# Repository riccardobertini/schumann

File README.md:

# Schumann Resonance Generator 🌍⚡  

This project was created with the idea of building **a simple yet interesting electronic device** capable of locally generating the most well-known **Schumann Resonance** frequencies, using the **Arduino** platform and easily available components.

> ⚠️ **Important note**  
> This project **is not a medical device** and makes no scientific claims. It is intended solely as an **electronic and educational experiment**.

---

## 📡 What Is the Schumann Resonance

The Schumann Resonance is a natural phenomenon discovered in the 1950s by physicist **Winfried Otto Schumann**.  
The Earth and the ionosphere behave like a kind of **natural cavity** in which certain electromagnetic frequencies can stabilize.

The most famous one is:
- **7.83 Hz** → fundamental frequency

Among the most well-known harmonics:
- **14.1 Hz**

These frequencies belong to the **ELF (Extremely Low Frequency)** category.

---

## 🤔 Why Does This Project Interest So Many People?

Online there are countless discussions, videos, and forums that attribute various **possible subjective effects** to the Schumann Resonance, often based on personal experiences.

The most common ones include:
- relaxation,
- improved sleep,
- stress reduction,
- increased concentration,
- a general sense of well-being.

👉 **Important:**  
These effects **are not scientifically proven**. However, curiosity and interest in these topics pushed me to experiment firsthand.

This project was born with exactly this mindset:  
**curiosity, DIY spirit, and conscious experimentation**.

---

## 🛠️ What This Generator Can Be Used For

The generator can be used in different contexts:

- **Educational Arduino project**  
  A great example of:
  - low-frequency signal generation,
  - interrupt handling for time synchronization,
  - control logic.

- **Personal experiment**  
  Some users use it in home environments (study, relaxation area, bedroom) to observe any subjective sensations.

- **Maker / DIY project**  
  Perfect as a base for:
  - adding a display,
  - Bluetooth or Wi-Fi control,
  - battery power,
  - integration into home automation projects.

- **Shielded or isolated environments**  
  Used by people working in spaces with strong electromagnetic shielding.

---

## ⚙️ Features

The device includes the following modes:

- 🔁 **Automatic dual frequency**
  - cyclic alternation between **7.83 Hz** and **14.1 Hz**

- 🎯 **Fixed frequency 7.83 Hz**

- 🎯 **Fixed frequency 14.1 Hz**

- 🌙 **LED shutdown during nighttime**
  - useful if the device is used in dark environments or during sleep hours

---

## 🔌 Hardware

The project uses:
- **Arduino Micro–compatible** microcontroller,
- simple electronic components,
- status LEDs,
- essential controls for mode selection.

The **electronic schematics** are available in the repository.

---

## 💻 Software

The firmware is developed in:
- **C++**
- **Arduino platform**

The code is designed to be:
- readable,
- easy to modify.

It manages:
- frequency generation,
- automatic switching,
- mode selection,
- LED control.

---

The repository includes:
- source code,
- electronic schematics,
- Gerber files for PCB manufacturing,
- STL files for enclosure creation.

Contributions, forks, and improvements are welcome 🚀

---

## 🖼️ Images of the Finished Project

Below are some images of the assembled and working device.

### General view

### Electronic board detail

### Device in operation

> 📌 Images are located in the `/images` folder of the repository.

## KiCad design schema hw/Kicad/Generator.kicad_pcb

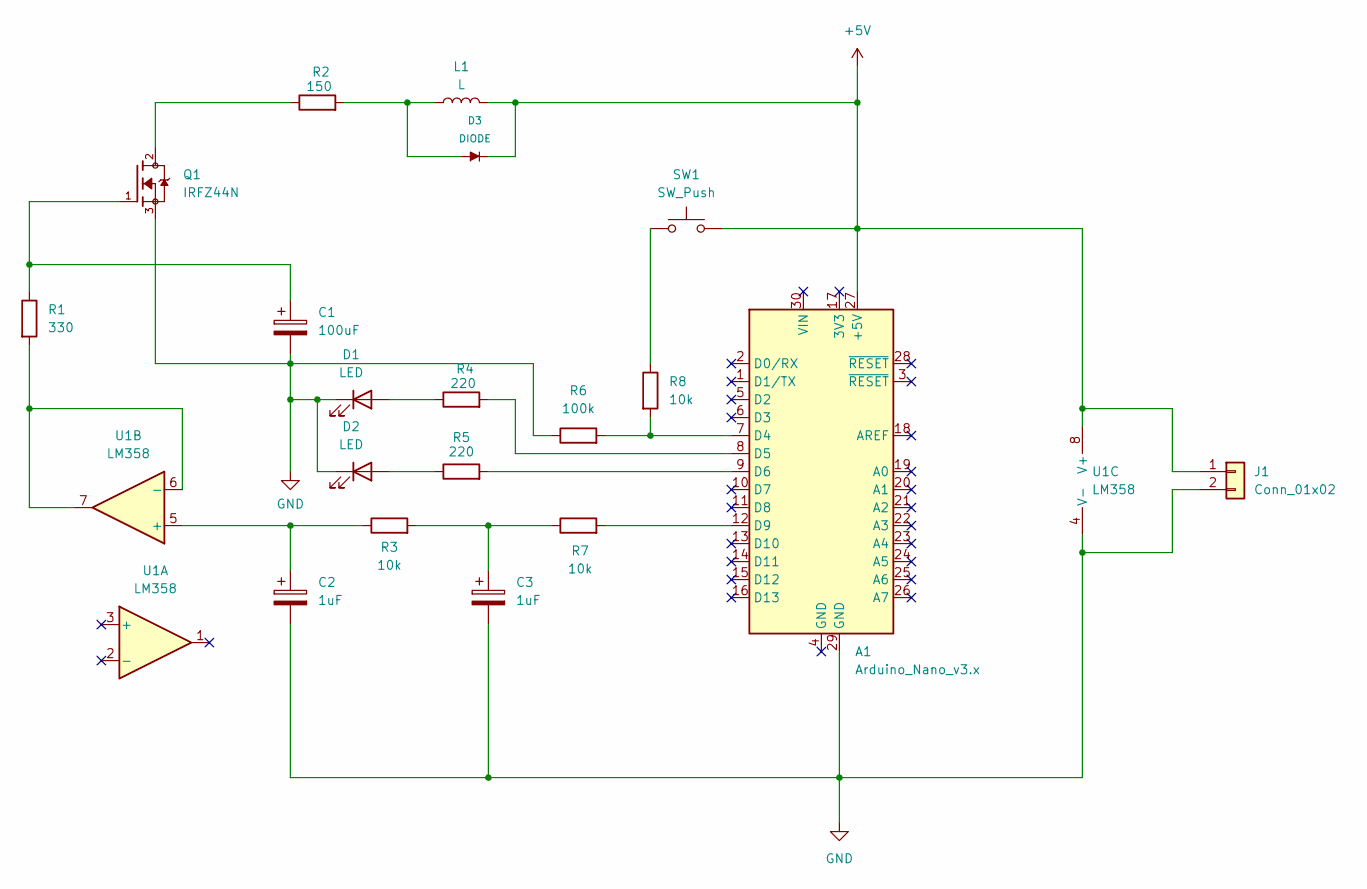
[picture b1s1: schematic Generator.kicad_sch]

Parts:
A1: Arduino_Nano_v3.x; Arduino_Nano
C1: 100uF; CP_Radial_D4.0mm_P1.50mm
C2, C3: 1uF; CP_Radial_D4.0mm_P1.50mm
D1, D2: LED; LED_D3.0mm
D3: DIODE; D_DO-35_SOD27_P7.62mm_Horizontal
J1: Conn_01x02; SolderWire-0.1sqmm_1x02_P3.6mm_D0.4mm_OD1mm
L1: L; Schuman_Coil
Q1: IRFZ44N; TO254P1016X419X2286-3; PARTREV 09/21/10
R1: 330; R_Axial_DIN0204_L3.6mm_D1.6mm_P5.08mm_Horizontal
R2: 150; R_Axial_DIN0204_L3.6mm_D1.6mm_P5.08mm_Horizontal
R3, R7, R8: 10k; R_Axial_DIN0204_L3.6mm_D1.6mm_P5.08mm_Horizontal
R4, R5: 220; R_Axial_DIN0204_L3.6mm_D1.6mm_P5.08mm_Horizontal
R6: 100k; R_Axial_DIN0204_L3.6mm_D1.6mm_P5.08mm_Horizontal
SW1: SW_Push; SW_PUSH_1P1T_6x3.5mm_H4.3_APEM_MJTP1243
U1: LM358

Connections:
+5V: A1.27 (+5V), D3.2 (K), J1.1, L1.2, SW1.2, U1.8 (V+)
GND: A1.29 (GND), C1.2, C2.2, C3.2, D1.1 (K), D2.1 (K), J1.2, Q1.3, R6.1, U1.4 (V-)
unnamed: A1.7 (D4), R6.2, R8.2
unnamed: A1.8 (D5), R4.2
unnamed: A1.9 (D6), R5.2
unnamed: A1.12 (D9), R7.2
unnamed: C1.1, Q1.1, R1.1
unnamed: C3.1, R3.2, R7.1
unnamed: D1.2 (A), R4.1
unnamed: D2.2 (A), R5.1
unnamed: D3.1 (A), L1.1, R2.2
unnamed: Q1.2, R2.1
unnamed: R8.1, SW1.1
unnamed: C2.1, R3.1, U1.5 (+)
unnamed: R1.2, U1.6 (-), U1.7

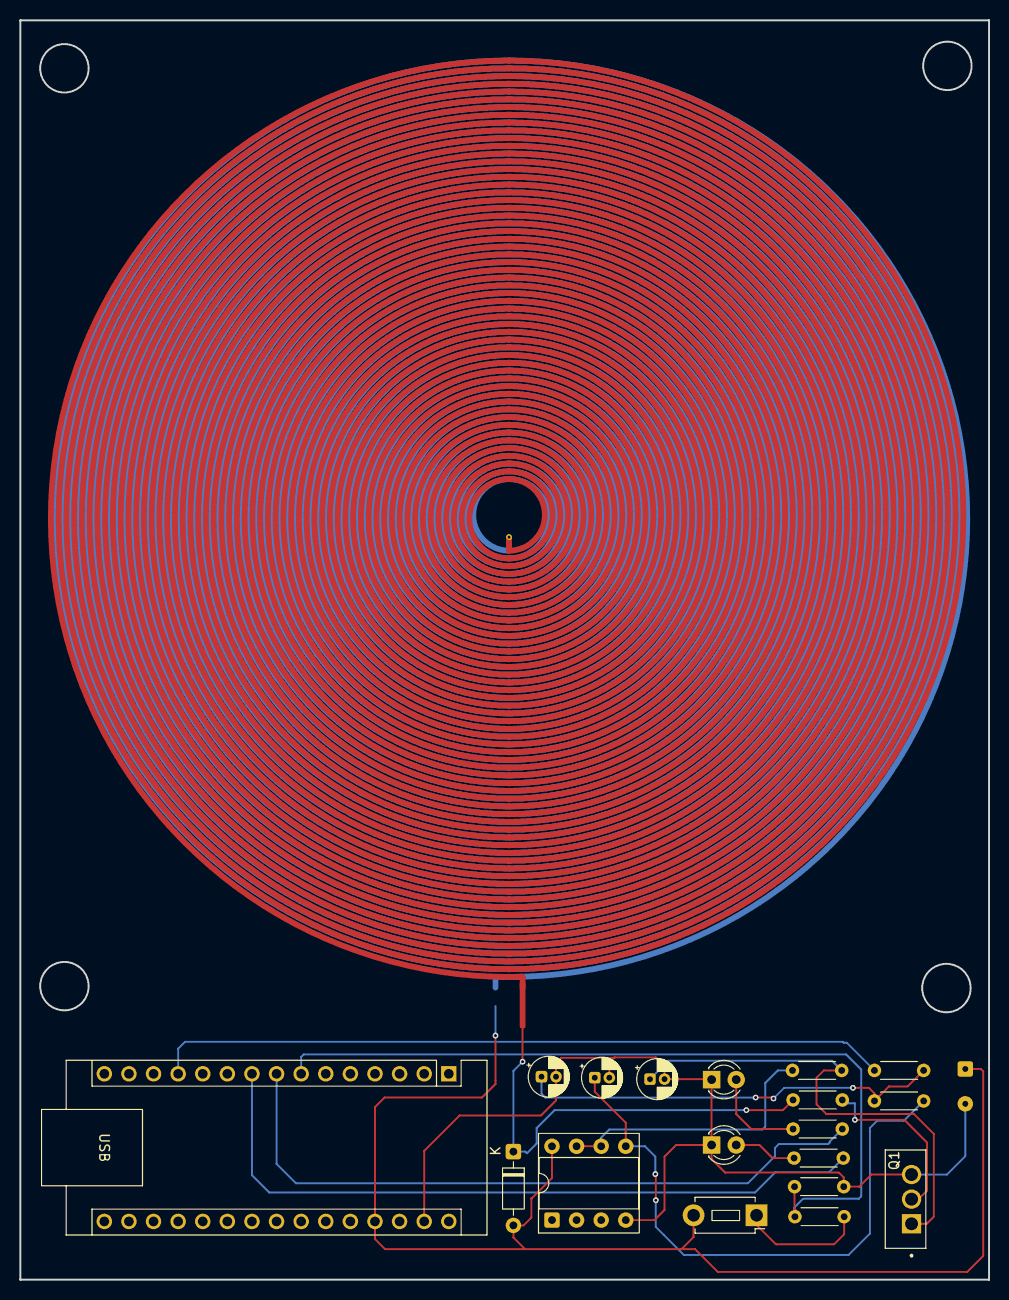
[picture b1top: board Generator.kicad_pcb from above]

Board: 2 copper layers, 100.0 x 130.0 mm, 20 parts (0 on the bottom side), 15 nets.

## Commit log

2026-02-05 Revise README with project overview and features
    Updated README to enhance project description and details.
2026-02-05 first import
